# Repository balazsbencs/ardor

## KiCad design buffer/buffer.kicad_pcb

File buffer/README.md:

# Ardor Guitar Input Buffer

This folder contains the minimal guitar input buffer for Ardor.

Use this board between a passive guitar and the Raspberry Pi Codec Zero. Do
not connect a passive guitar directly to the Codec Zero input.

## KiCad project

Open [`buffer.kicad_pro`](buffer.kicad_pro) in KiCad to view or edit the
schematic and PCB.

Connect the guitar jack to `GUITAR_IN`. Connect `GUITAR_OUT` to the Codec Zero
input. Follow [`buffer.kicad_sch`](buffer.kicad_sch) for power and ground.

## JLCPCB assembly

The [`jlcpcb/production_files/`](jlcpcb/production_files/) folder contains
order-ready files for SMD assembly:

- [`GERBER-buffer.zip`](jlcpcb/production_files/GERBER-buffer.zip) contains the PCB files.
- [`BOM-buffer.csv`](jlcpcb/production_files/BOM-buffer.csv) contains the parts list.
- [`CPL-buffer.csv`](jlcpcb/production_files/CPL-buffer.csv) contains the part placement list.

Upload the Gerber, BOM, and CPL files to a JLCPCB PCB assembly order. Review
the parts and placement before you order.

The production files cover the SMD parts only. They do not include audio
jacks, wires, connectors, or enclosure parts. Add these parts after the board
arrives.

The larger [`hardware/control-io`](../hardware/control-io/README.md) and
[`hardware/integrated-codec-revc`](../hardware/integrated-codec-revc/README.md)
designs include their own guitar input stages. Choose one input design. Do not
place the standalone buffer in series with either design.

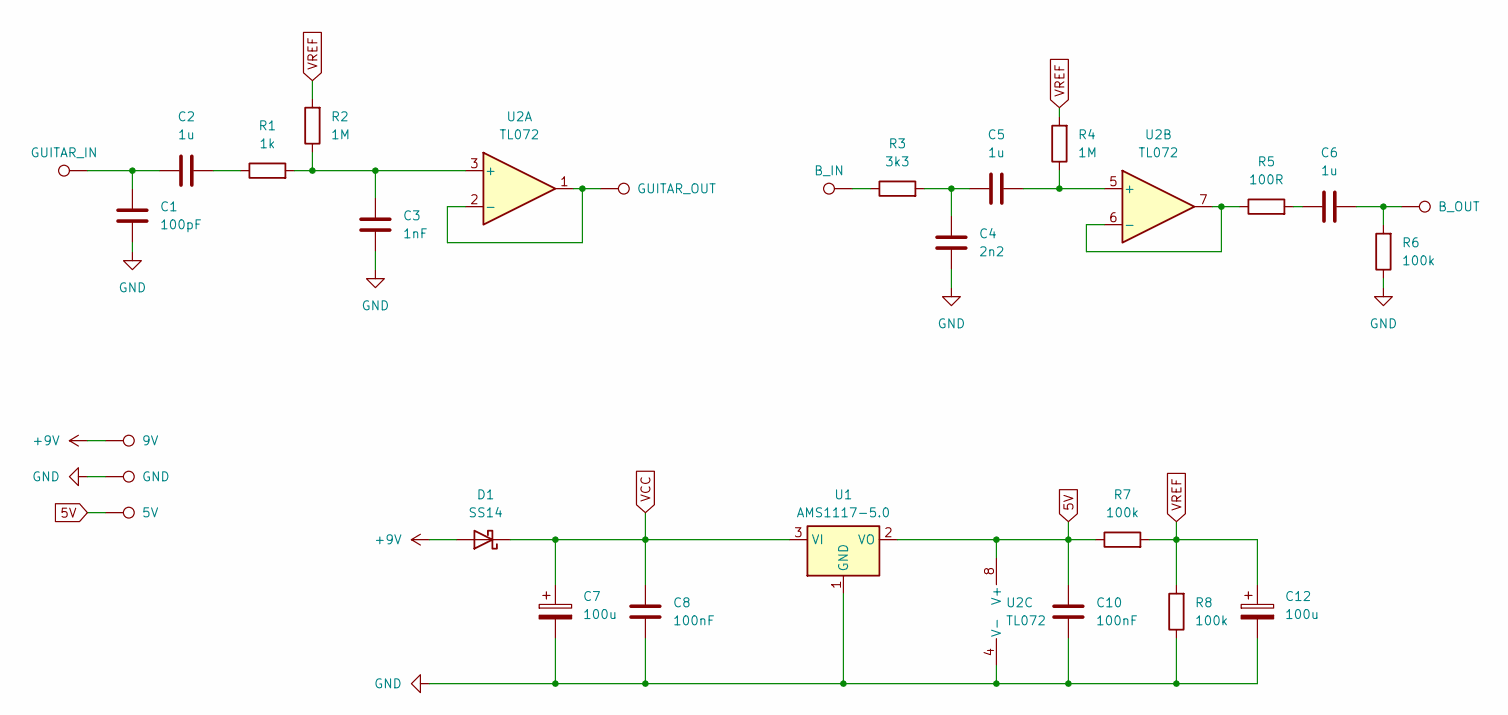
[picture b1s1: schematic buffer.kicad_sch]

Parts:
5V1: 5V; Pin_D1.0mm_L10.0mm_LooseFit
9V1: 9V; Pin_D1.0mm_L10.0mm_LooseFit
BUFFER_IN1: B_IN; Pin_D1.0mm_L10.0mm_LooseFit
C1: 100pF; C_0603_1608Metric
C2, C5, C6: 1u; C_0603_1608Metric
C3: 1nF; C_0603_1608Metric
C4: 2n2; C_0603_1608Metric
C7, C12: 100u; CP_Radial_D6.3mm_P2.50mm
C8, C10: 100nF; C_0603_1608Metric
D1: SS14; D_SMA
GIN1: GUITAR_IN; Pin_D1.0mm_L10.0mm_LooseFit
GND1: GND; Pin_D1.0mm_L10.0mm_LooseFit
GOUT1: GUITAR_OUT; Pin_D1.0mm_L10.0mm_LooseFit
OUT1: B_OUT; Pin_D1.0mm_L10.0mm_LooseFit
R1: 1k; R_0603_1608Metric
R2, R4: 1M; R_0603_1608Metric
R3: 3k3; R_0603_1608Metric
R5: 100R; R_0603_1608Metric
R6, R7, R8: 100k; R_0603_1608Metric
U1: AMS1117-5.0; SOT-223-3_TabPin2
U2: TL072; SOIC-8_3.9x4.9mm_P1.27mm

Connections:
5V: 5V1.1, C10.1, R7.1, U1.2 (VO), U2.8 (V+)
+9V: 9V1.1, D1.2 (A)
GND: C1.2, C3.2, C4.2, C7.2, C8.2, C10.2, C12.2, GND1.1, R6.1, R8.1, U1.1 (GND), U2.4 (V-)
unnamed: BUFFER_IN1.1, R3.1
unnamed: C1.1, C2.1, GIN1.1
unnamed: C2.2, R1.1
unnamed: C4.1, C5.1, R3.2
unnamed: C6.1, R5.2
unnamed: C6.2, OUT1.1, R6.2
unnamed: C3.1, R1.2, R2.1, U2.3 (+)
unnamed: GOUT1.1, U2.1, U2.2 (-)
unnamed: C5.2, R4.1, U2.5 (+)
unnamed: R5.1, U2.6 (-), U2.7
VCC: C7.1, C8.1, D1.1 (K), U1.3 (VI)
VREF: C12.1, R2.2, R4.2, R7.2, R8.2

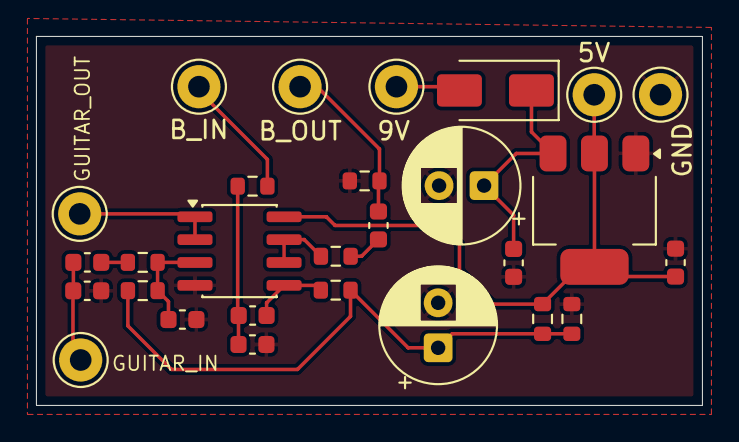
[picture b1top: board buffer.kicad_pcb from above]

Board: 2 copper layers, 37.0 x 20.5 mm, 28 parts (0 on the bottom side), 15 nets.

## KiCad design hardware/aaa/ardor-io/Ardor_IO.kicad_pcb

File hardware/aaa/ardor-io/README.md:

# Ardor Codec Zero I/O

Open **Ardor_IO.kicad_pro** in KiCad 9. The root schematic opens five functional sheets. **Ardor_IO.kicad_pcb** is the routed 68 × 46 mm compact board (45.7% less area than the previous 90 × 64 mm board; 60.9% less than the original 100 × 80 mm placement).

- **Ardor_IO.pdf** — printable six-sheet schematic.
- **BOM.csv** — component values, exact SMT manufacturer/JLCPCB part numbers and footprints.
- **[assembly/](assembly/README.md)** — stocked JLCPCB selections, BOM/CPL and Gerbers for **two boards, top-side SMT only**, plus the separate hand-assembly list.
- **DESIGN_NOTES.md** — wiring, GPIOs, signal levels, firmware sequence, layout guidance and production-release tests.
- **SOURCES.md** — primary data sheets and interface references.
- **verification/** — schematic ERC, exported netlist and connectivity audit.
- **routing/** — current board previews, placement coordinates, zero-violation DRC/parity report, pad/net audit and routing source/session. See [routing/README.md](routing/README.md).
- **footprints/** — project-local snapshots of the original package footprints, preserving their geometry across KiCad 9 library versions.
- **pcb-plan/** — historical, unrouted 100 × 80 mm placement; superseded by the current board.

Uses 5 V from the Pi, a 100 kΩ passive expression pedal, mono 6.3 mm line out, stereo headphones, DIN MIDI in and an internal feed to the separate amp circuit.

Rev A is a checked engineering prototype schematic, not a bench-qualified production release. Read the integration and release notes before building. Panel connector models and stack height are mechanical selections to be finalized with your PCB/enclosure.

The compact layout retains all 95 schematic components and the existing panel-harness interfaces. Connector functions/pins and testpoint signals are on front silkscreen; JP301 shunt instructions are on the back. Component references remain on F.Fab. Four M3 holes are provisional enclosure mounts, not a verified Raspberry Pi mounting pattern. Confirm mechanical fit and stack height before ordering.

C401/C402/C502/C601/C602 are now 10 µF / 50 V Samsung X7R ceramic capacitors (CL31B106KBHNNNE, JLCPCB C89632) in standard 1206 footprints. See [SMD capacitor selection](routing/SMD_CAPACITORS.md).

Review fixes (29 September 2026): Q501 is AO3400A; C501 is Panasonic EEEFK1C470P with manufacturer-specific local lands. The aluminium enclosure is bonded through audio jack sleeves; the MIDI input shell is insulated and unconnected. See [fix verification](review/FIXES.md) and the updated [connected single-page schematic](review/Ardor_IO_connected.pdf).

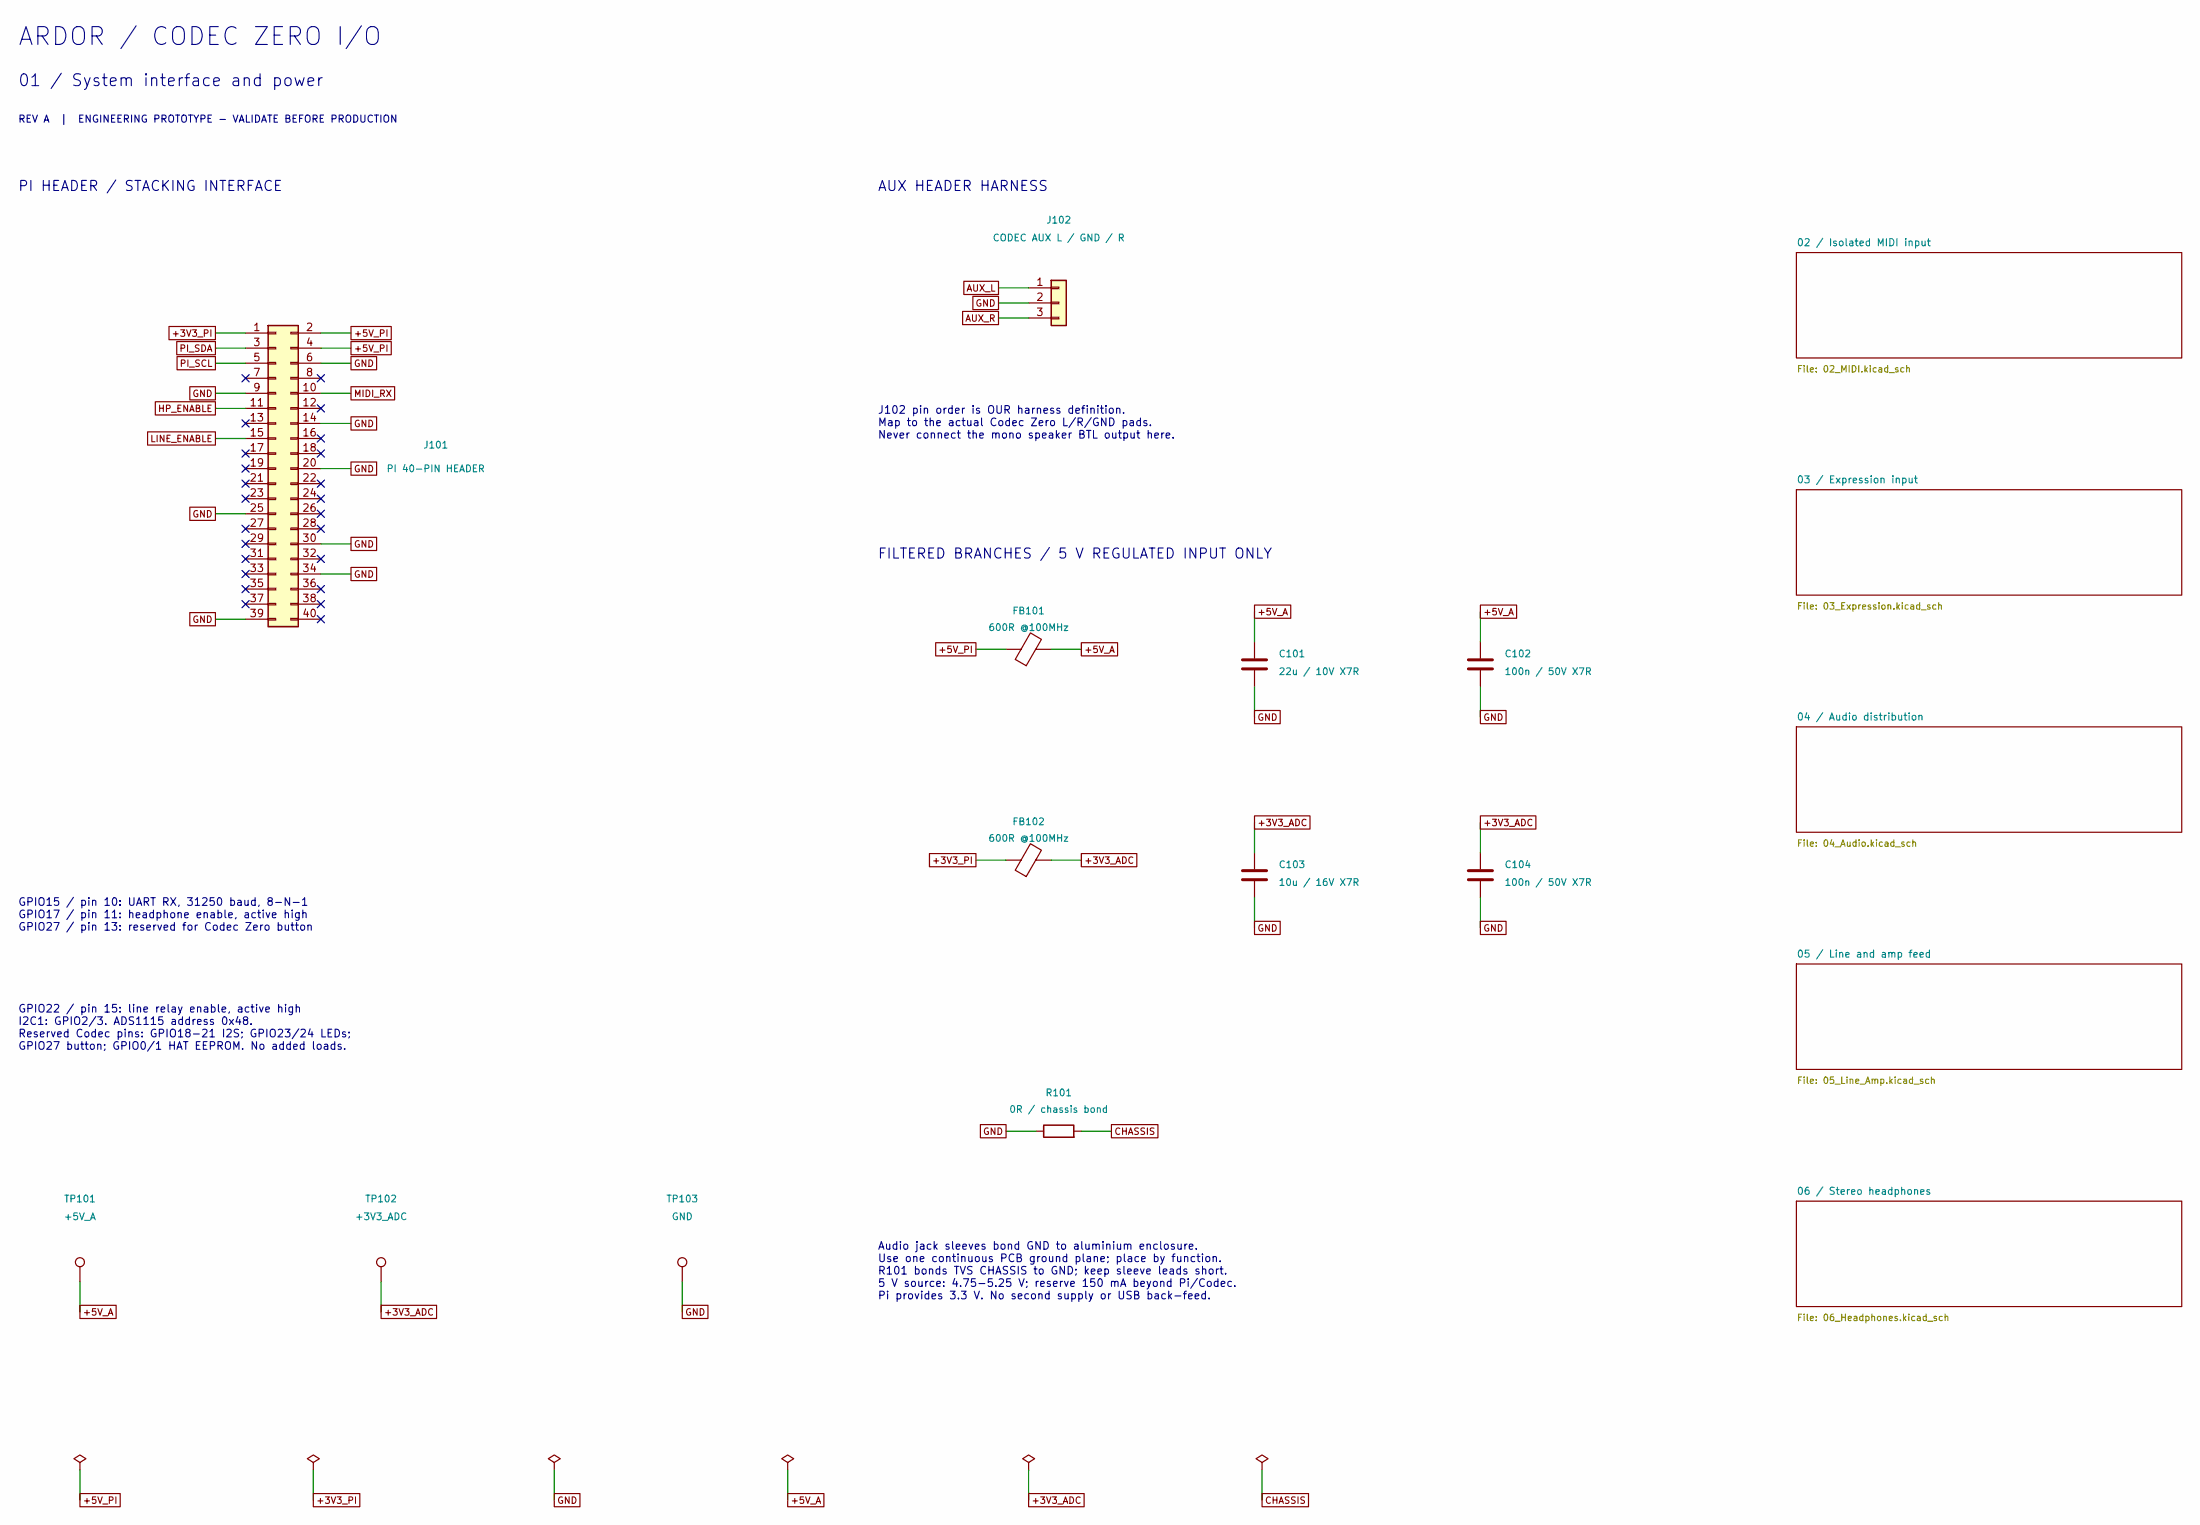
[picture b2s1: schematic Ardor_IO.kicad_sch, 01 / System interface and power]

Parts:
C101: 22u / 10V X7R; C_0805_2012Metric; MPN Murata GRM21BZ71A226ME15L; JLCPCB Part # C907991
C102, C104: 100n / 50V X7R; C_0603_1608Metric; MPN YAGEO CC0603KRX7R9BB104; JLCPCB Part # C14663
C103: 10u / 16V X7R; C_0805_2012Metric; MPN Samsung CL21B106KOQNNNE; JLCPCB Part # C95841
FB101: 600R @100MHz; L_0805_2012Metric; MPN Murata BLM21PG601SN1D; JLCPCB Part # C41556732
FB102: 600R @100MHz; R_0603_1608Metric; MPN Murata BLM18AG601SN1D; JLCPCB Part # C19330
J101: PI 40-PIN HEADER; PinSocket_2x20_P2.54mm_Vertical; MPN Samtec SSQ-120-03-G-D (verify stack hei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
J102: CODEC AUX L / GND / R; PinHeader_1x03_P2.54mm_Vertical
R101: 0R / chassis bond; R_1206_3216Metric; MPN UNI-ROYAL 1206W4F0000T5E; JLCPCB Part # C17888
TP101: +5V_A; TestPoint_Pad_D1.5mm
TP102: +3V3_ADC; TestPoint_Pad_D1.5mm
TP103: GND; TestPoint_Pad_D1.5mm

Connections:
+3V3_ADC: C103.1, C104.1, FB102.2, TP102.1; also elsewhere on the board
+3V3_PI: FB102.1, J101.1; also elsewhere on the board
+5V_A: C101.1, C102.1, FB101.2, TP101.1; also elsewhere on the board
+5V_PI: FB101.1, J101.2, J101.4; also elsewhere on the board
AUX_L: J102.1; also elsewhere on the board
AUX_R: J102.3; also elsewhere on the board
CHASSIS: R101.2; also elsewhere on the board
GND: C101.2, C102.2, C103.2, C104.2, J101.6, J101.9, J101.14, J101.20, J101.25, J101.30, J101.34, J101.39, J102.2, R101.1, TP103.1; also elsewhere on the board
HP_ENABLE: J101.11; also elsewhere on the board
LINE_ENABLE: J101.15; also elsewhere on the board
MIDI_RX: J101.10; also elsewhere on the board
PI_SCL: J101.5; also elsewhere on the board
PI_SDA: J101.3; also elsewhere on the board

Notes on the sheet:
ARDOR / CODEC ZERO I/O
01 / System interface and power
REV A | ENGINEERING PROTOTYPE - VALIDATE BEFORE PRODUCTION
PI HEADER / STACKING INTERFACE
GPIO15 / pin 10: UART RX, 31250 baud, 8-N-1 GPIO17 / pin 11: headphone enable, active high GPIO27 / pin 13: reserved for Codec Zero button
GPIO22 / pin 15: line relay enable, active high I2C1: GPIO2/3. ADS1115 address 0x48. Reserved Codec pins: GPIO18-21 I2S; GPIO23/24 LEDs; GPIO27 button; GPIO0/1 HAT EEPROM. No added loads.
AUX HEADER HARNESS
J102 pin order is OUR harness definition. Map to the actual Codec Zero L/R/GND pads. Never connect the mono speaker BTL output here.
FILTERED BRANCHES / 5 V REGULATED INPUT ONLY
Audio jack sleeves bond GND to aluminium enclosure. Use one continuous PCB ground plane; place by function. R101 bonds TVS CHASSIS to GND; keep sleeve leads short. 5 V source: 4.75-5.25 V; reserve 150 mA beyond Pi/Codec. Pi provides 3.3 V. No second supply or USB back-feed.

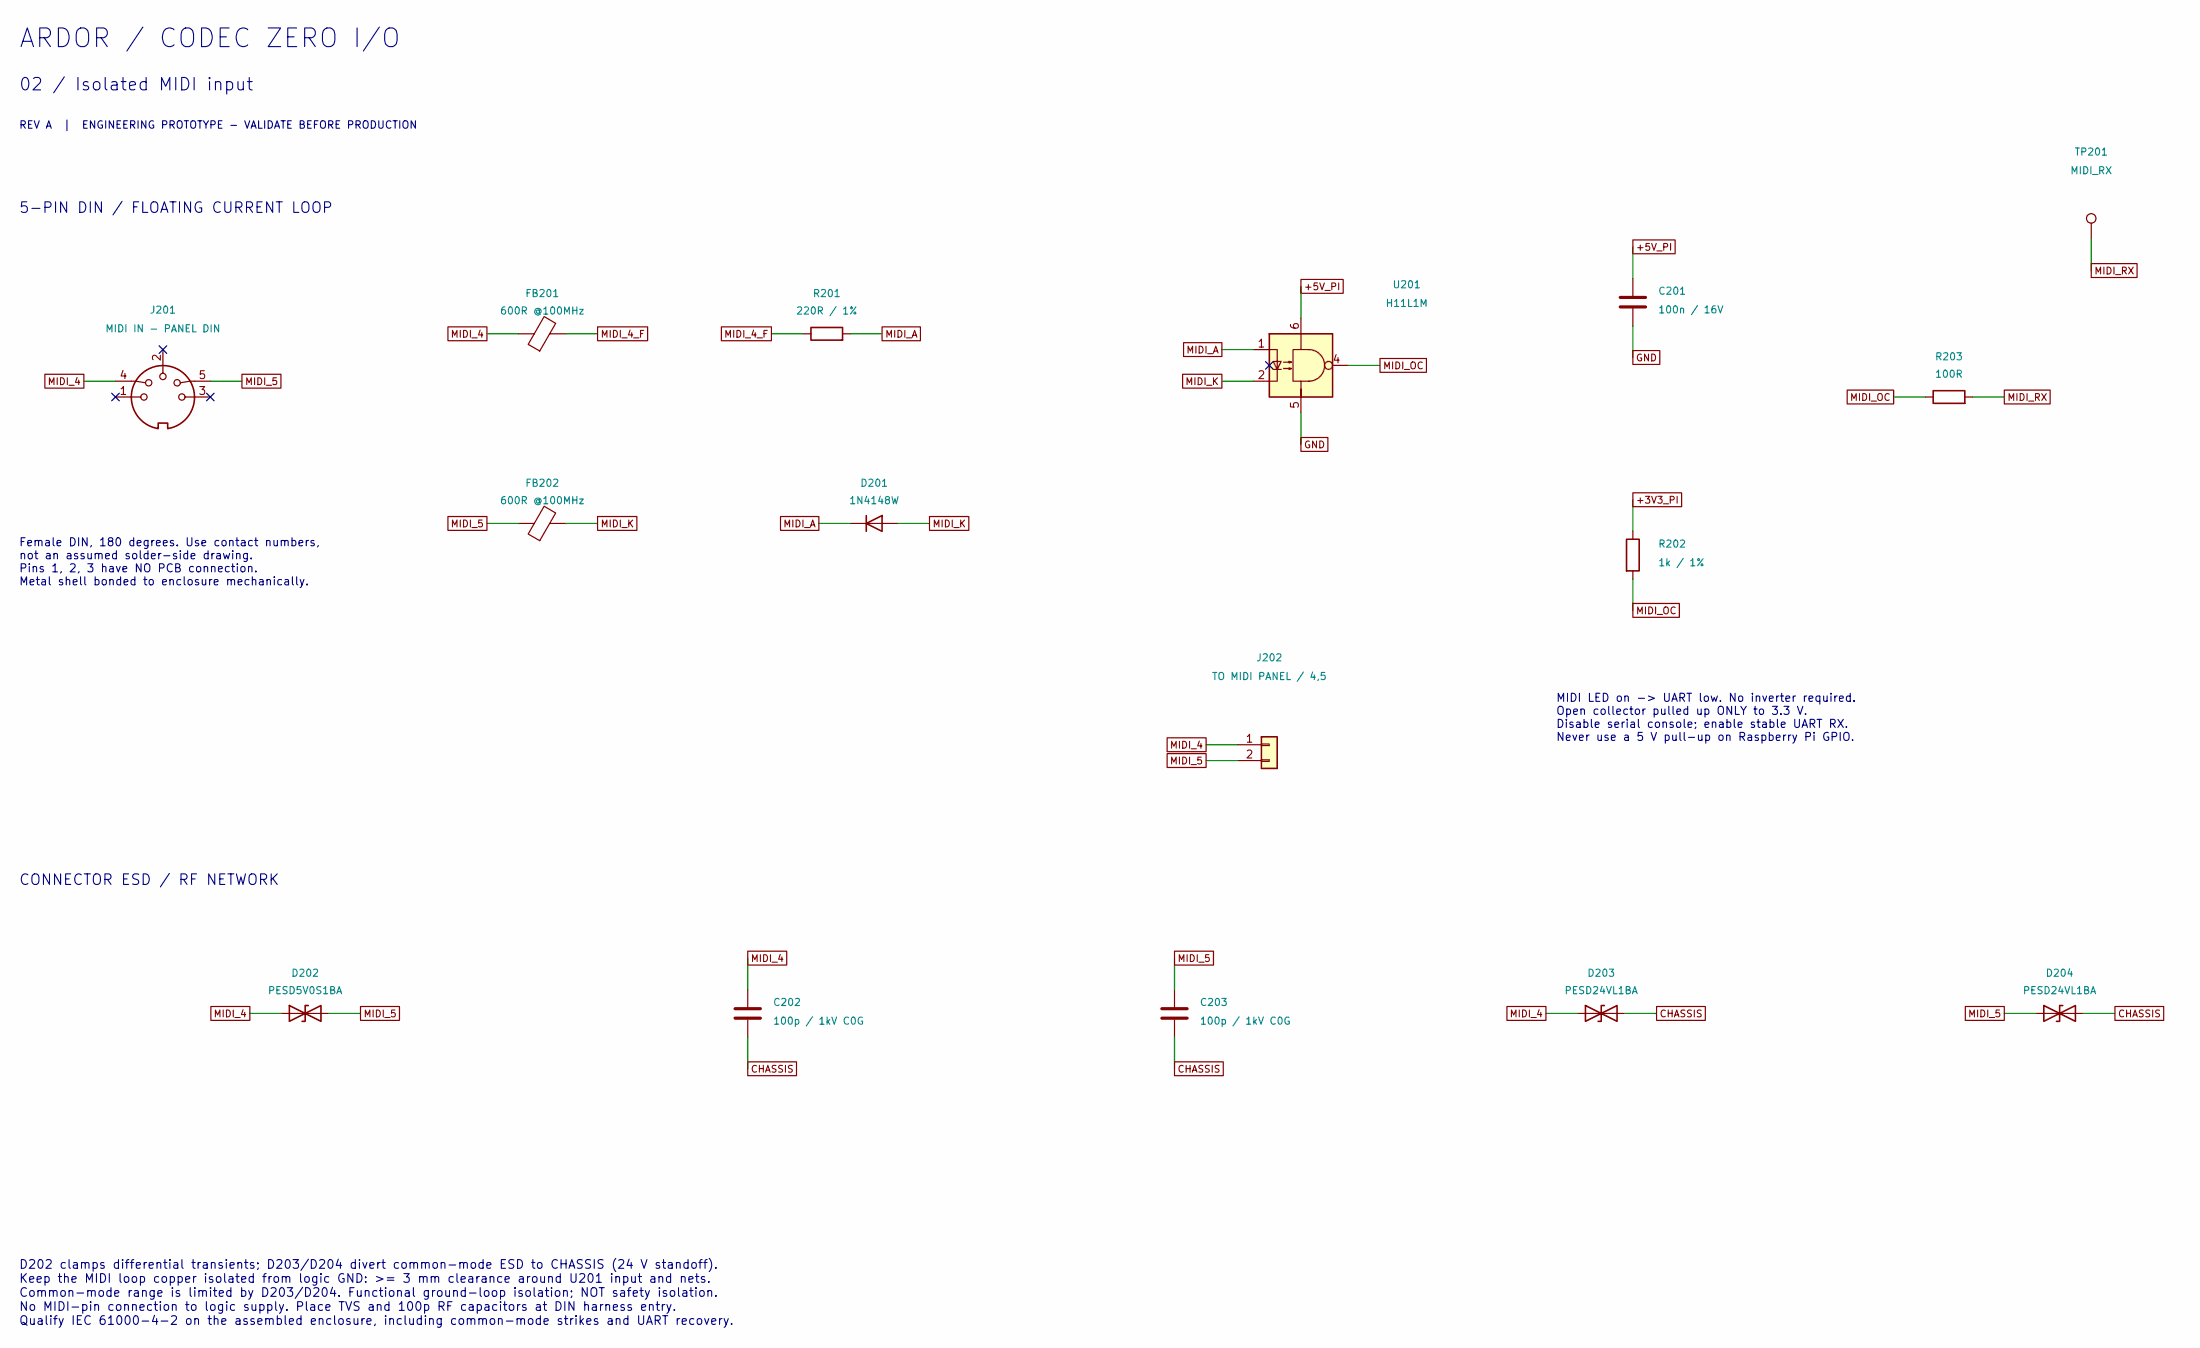
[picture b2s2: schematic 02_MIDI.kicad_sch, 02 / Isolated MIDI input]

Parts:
C201: 100n / 16V; C_0603_1608Metric
C202, C203: 100p / 1kV C0G; C_1206_3216Metric
D201: 1N4148W; D_SOD-123; MPN 1N4148W
D202: PESD5V0S1BA; D_SOD-323; MPN Nexperia PESD5V0S1BA
D203, D204: PESD24VL1BA; D_SOD-323; MPN Nexperia PESD24VL1BA
FB201, FB202: 600R @100MHz; R_0603_1608Metric; MPN Murata BLM18AG601SN1D
J201: MIDI IN - PANEL DIN
J202: TO MIDI PANEL / 4,5; PinHeader_1x02_P2.54mm_Vertical
R201: 220R / 1%; R_0603_1608Metric
R202: 1k / 1%; R_0603_1608Metric
R203: 100R; R_0603_1608Metric
TP201: MIDI_RX; TestPoint_Pad_D1.5mm
U201: H11L1M; DIP-6_W7.62mm; MPN onsemi H11L1M

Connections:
+3V3_PI: R202.1; also elsewhere on the board
+5V_PI: C201.1, U201.6; also elsewhere on the board
CHASSIS: C202.2, C203.2, D203.2 (A2), D204.2 (A2); also elsewhere on the board
GND: C201.2, U201.5; also elsewhere on the board
MIDI_4: C202.1, D202.1 (A1), D203.1 (A1), FB201.1, J201.4, J202.1
MIDI_4_F: FB201.2, R201.1
MIDI_5: C203.1, D202.2 (A2), D204.1 (A1), FB202.1, J201.5, J202.2
MIDI_A: D201.1 (K), R201.2, U201.1
MIDI_K: D201.2 (A), FB202.2, U201.2
MIDI_OC: R202.2, R203.1, U201.4
MIDI_RX: R203.2, TP201.1; also elsewhere on the board

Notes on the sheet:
ARDOR / CODEC ZERO I/O
02 / Isolated MIDI input
REV A | ENGINEERING PROTOTYPE - VALIDATE BEFORE PRODUCTION
5-PIN DIN / FLOATING CURRENT LOOP
Female DIN, 180 degrees. Use contact numbers, not an assumed solder-side drawing. Pins 1, 2, 3 have NO PCB connection. Metal shell bonded to enclosure mechanically.
MIDI LED on -> UART low. No inverter required. Open collector pulled up ONLY to 3.3 V. Disable serial console; enable stable UART RX. Never use a 5 V pull-up on Raspberry Pi GPIO.
CONNECTOR ESD / RF NETWORK
D202 clamps differential transients; D203/D204 divert common-mode ESD to CHASSIS (24 V standoff). Keep the MIDI loop copper isolated from logic GND: >= 3 mm clearance around U201 input and nets. Common-mode range is limited by D203/D204. Functional ground-loop isolation; NOT safety isolation. No MI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

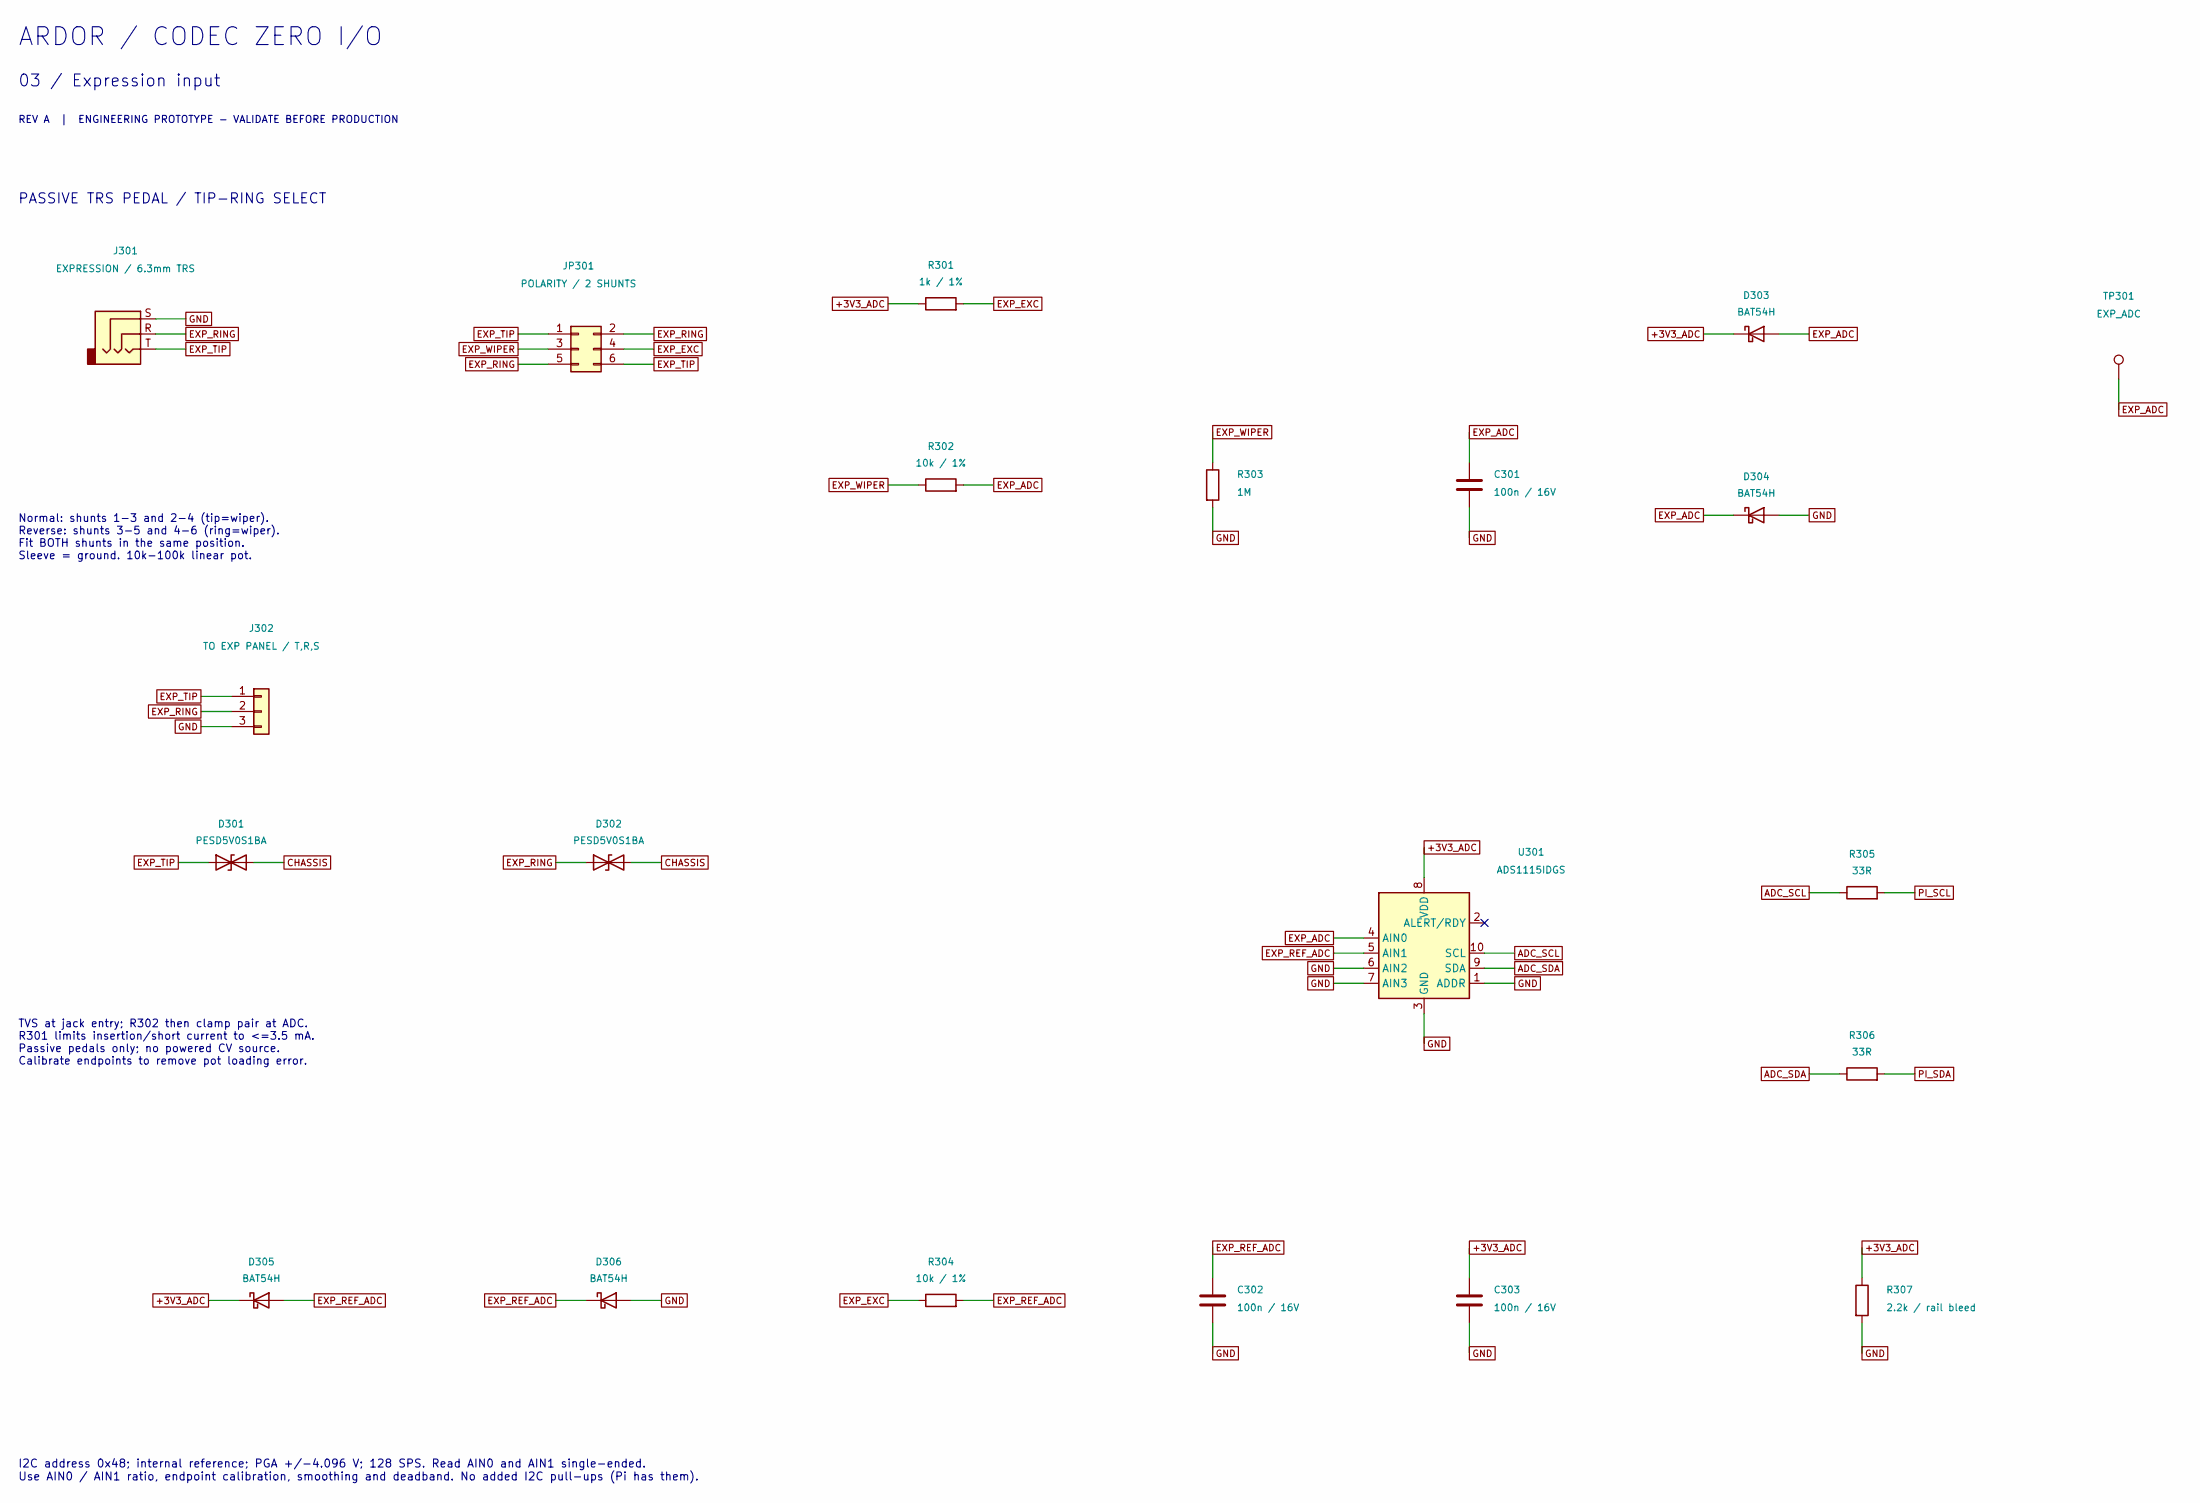
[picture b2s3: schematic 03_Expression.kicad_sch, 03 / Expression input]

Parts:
C301, C302, C303: 100n / 16V; C_0603_1608Metric
D301, D302: PESD5V0S1BA; D_SOD-323; MPN Nexperia PESD5V0S1BA
D303, D304, D305, D306: BAT54H; D_SOD-123F; MPN Nexperia BAT54H,115
J301: EXPRESSION / 6.3mm TRS
J302: TO EXP PANEL / T,R,S; PinHeader_1x03_P2.54mm_Vertical
JP301: POLARITY / 2 SHUNTS; PinHeader_2x03_P2.54mm_Vertical
R301: 1k / 1%; R_0603_1608Metric
R302, R304: 10k / 1%; R_0603_1608Metric
R303: 1M; R_0603_1608Metric
R305, R306: 33R; R_0603_1608Metric
R307: 2.2k / rail bleed; R_0603_1608Metric
TP301: EXP_ADC; TestPoint_Pad_D1.5mm
U301: ADS1115IDGS; VSSOP-10_3x3mm_P0.5mm; MPN TI ADS1115IDGSR

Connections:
+3V3_ADC: C303.1, D303.1 (K), D305.1 (K), R301.1, R307.1, U301.8 (VDD); also elsewhere on the board
ADC_SCL: R305.1, U301.10 (SCL)
ADC_SDA: R306.1, U301.9 (SDA)
CHASSIS: D301.2 (A2), D302.2 (A2); also elsewhere on the board
EXP_ADC: C301.1, D303.2 (A), D304.1 (K), R302.2, TP301.1, U301.4 (AIN0)
EXP_EXC: JP301.4, R301.2, R304.1
EXP_REF_ADC: C302.1, D305.2 (A), D306.1 (K), R304.2, U301.5 (AIN1)
EXP_RING: D302.1 (A1), J301.R, J302.2, JP301.2, JP301.5
EXP_TIP: D301.1 (A1), J301.T, J302.1, JP301.1, JP301.6
EXP_WIPER: JP301.3, R302.1, R303.1
GND: C301.2, C302.2, C303.2, D304.2 (A), D306.2 (A), J301.S, J302.3, R303.2, R307.2, U301.1 (ADDR), U301.3 (GND), U301.6 (AIN2), U301.7 (AIN3); also elsewhere on the board
PI_SCL: R305.2; also elsewhere on the board
PI_SDA: R306.2; also elsewhere on the board

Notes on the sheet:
ARDOR / CODEC ZERO I/O
03 / Expression input
REV A | ENGINEERING PROTOTYPE - VALIDATE BEFORE PRODUCTION
PASSIVE TRS PEDAL / TIP-RING SELECT
Normal: shunts 1-3 and 2-4 (tip=wiper). Reverse: shunts 3-5 and 4-6 (ring=wiper). Fit BOTH shunts in the same position. Sleeve = ground. 10k-100k linear pot.
TVS at jack entry; R302 then clamp pair at ADC. R301 limits insertion/short current to <=3.5 mA. Passive pedals only; no powered CV source. Calibrate endpoints to remove pot loading error.
I2C address 0x48; internal reference; PGA +/-4.096 V; 128 SPS. Read AIN0 and AIN1 single-ended. Use AIN0 / AIN1 ratio, endpoint calibration, smoothing and deadband. No added I2C pull-ups (Pi has them).

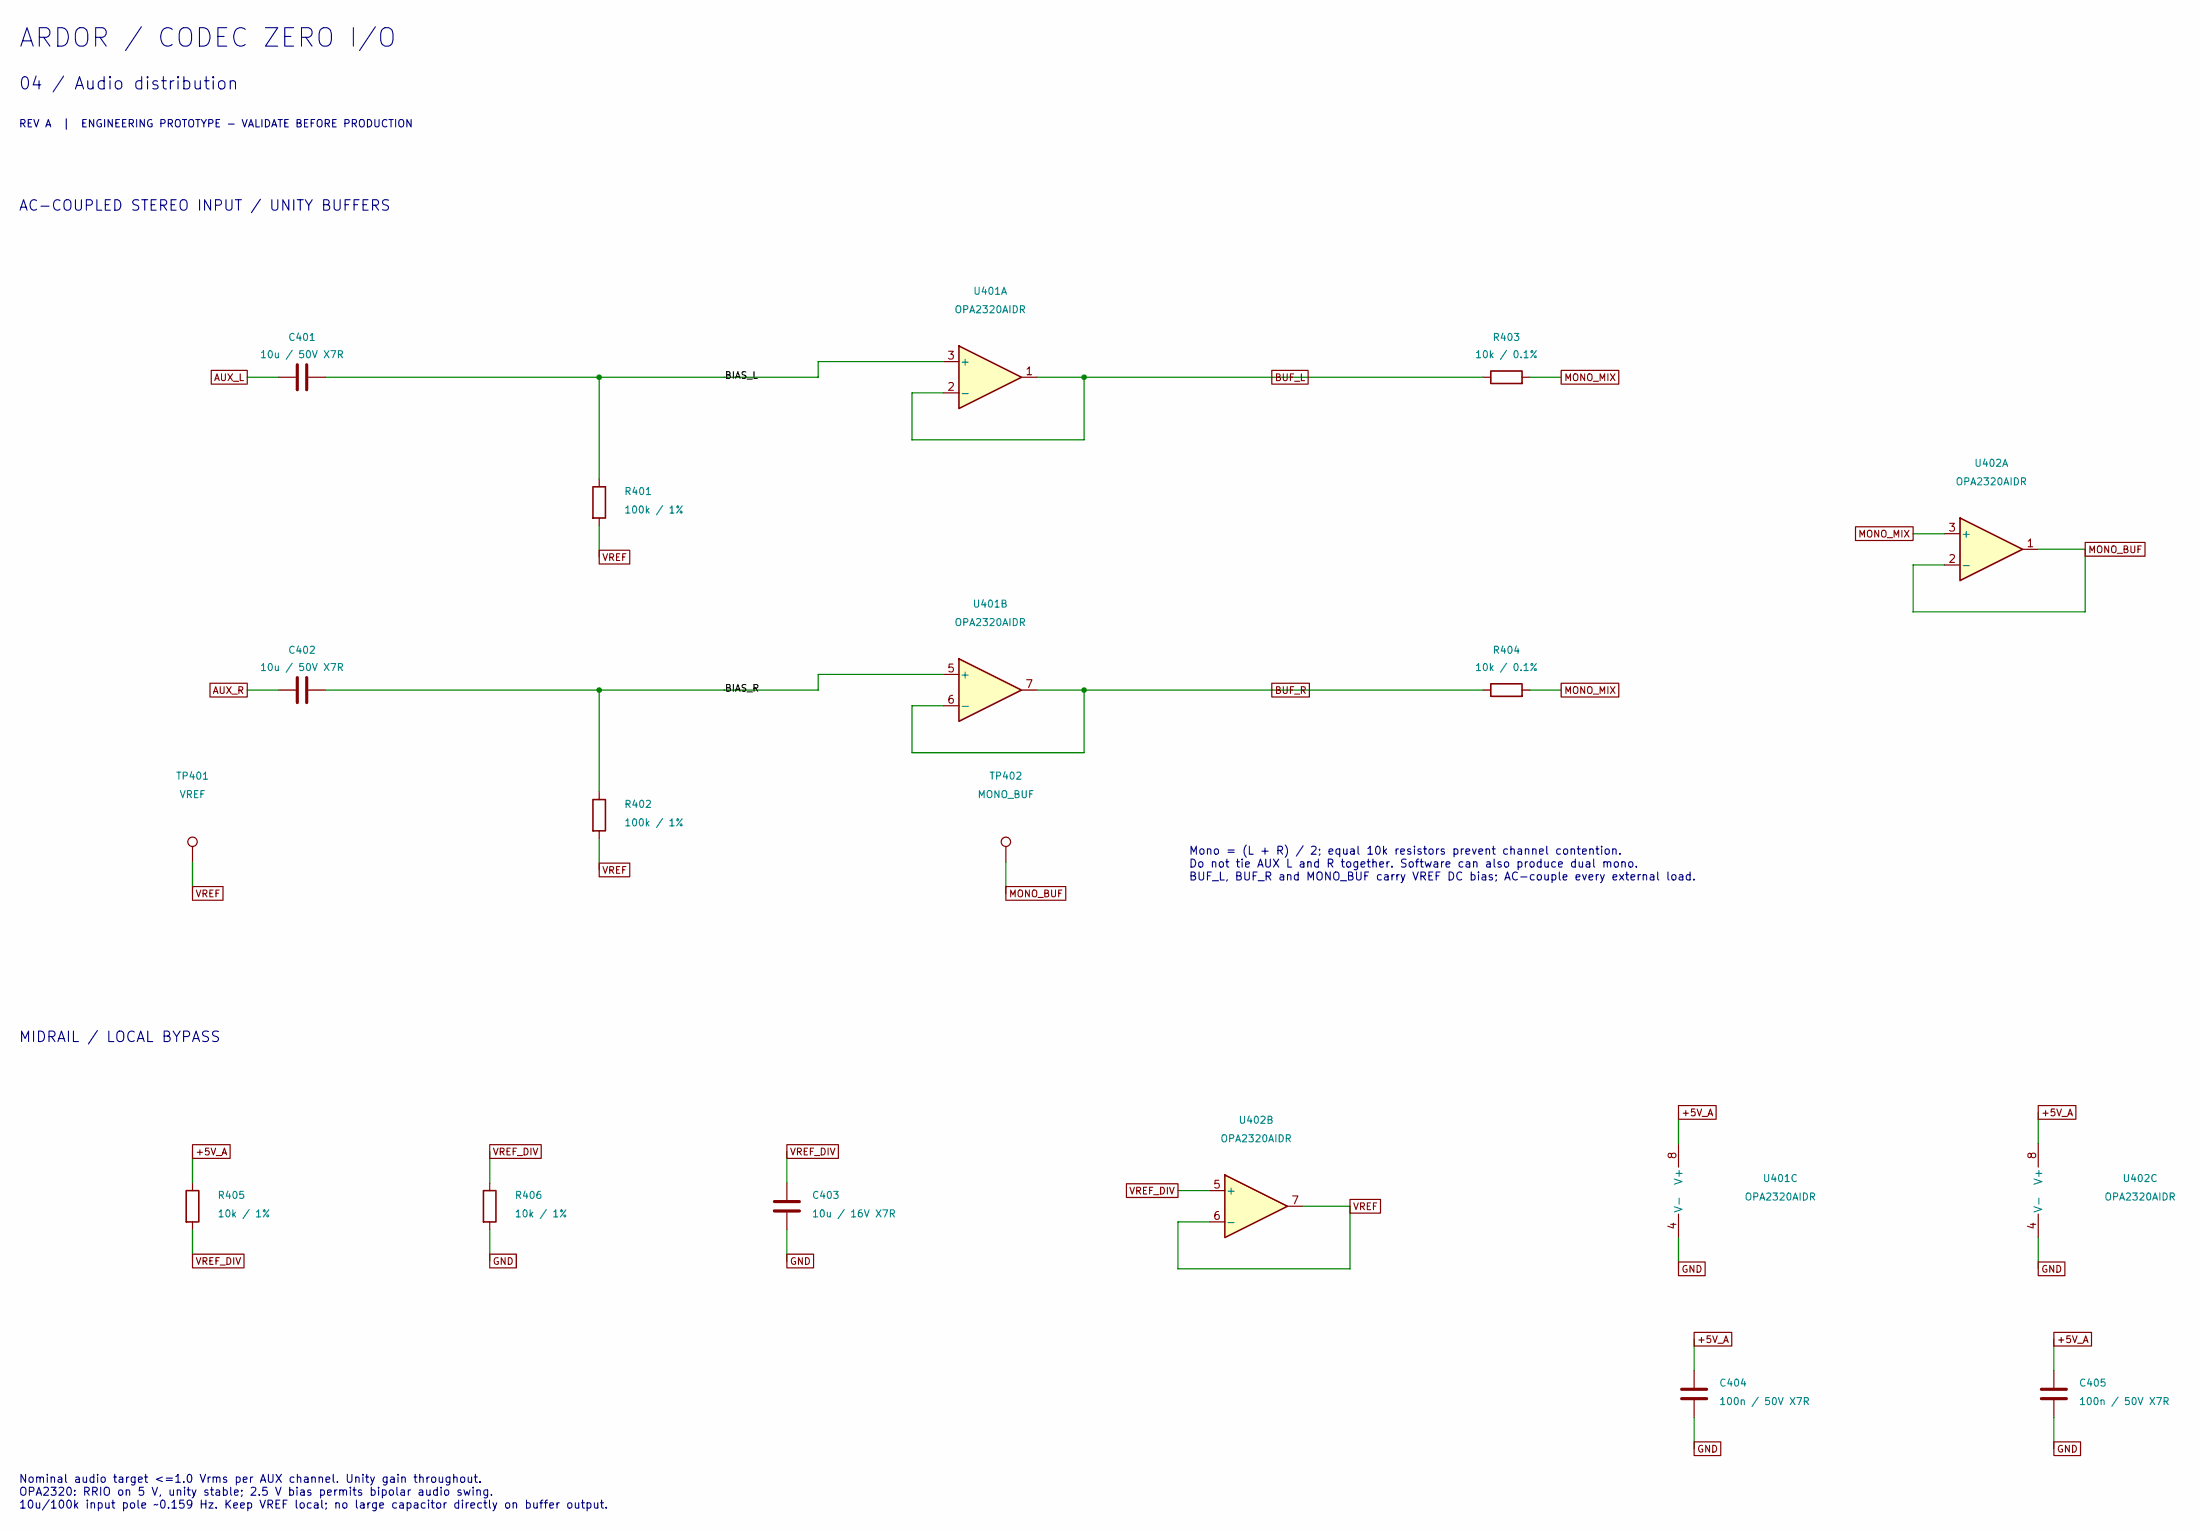
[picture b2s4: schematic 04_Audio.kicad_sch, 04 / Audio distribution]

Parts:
C401, C402: 10u / 50V X7R; C_1206_3216Metric; MPN Samsung CL31B106KBHNNNE; JLCPCB Part # C89632
C403: 10u / 16V X7R; C_0805_2012Metric; MPN Samsung CL21B106KOQNNNE; JLCPCB Part # C95841
C404, C405: 100n / 50V X7R; C_0603_1608Metric; MPN YAGEO CC0603KRX7R9BB104; JLCPCB Part # C14663
R401, R402: 100k / 1%; R_0603_1608Metric; MPN UNI-ROYAL 0603WAF1003T5E; JLCPCB Part # C25803
R403, R404: 10k / 0.1%; R_0603_1608Metric; MPN YAGEO RT0603BRD0710KL; JLCPCB Part # C95204
R405, R406: 10k / 1%; R_0603_1608Metric; MPN UNI-ROYAL 0603WAF1002T5E; JLCPCB Part # C25804
TP401: VREF; TestPoint_Pad_D1.5mm
TP402: MONO_BUF; TestPoint_Pad_D1.5mm
U401, U402: OPA2320AIDR; SOIC-8_3.9x4.9mm_P1.27mm; MPN TI OPA2320AIDR; JLCPCB Part # C2863402

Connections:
+5V_A: C404.1, C405.1, R405.1, U401.8 (V+), U402.8 (V+); also elsewhere on the board
/04 / Audio distribution/BIAS_L: C401.2, R401.1, U401.3 (+)
/04 / Audio distribution/BIAS_R: C402.2, R402.1, U401.5 (+)
AUX_L: C401.1; also elsewhere on the board
AUX_R: C402.1; also elsewhere on the board
BUF_L: R403.1, U401.1, U401.2 (-); also elsewhere on the board
BUF_R: R404.1, U401.6 (-), U401.7; also elsewhere on the board
GND: C403.2, C404.2, C405.2, R406.2, U401.4 (V-), U402.4 (V-); also elsewhere on the board
MONO_BUF: TP402.1, U402.1, U402.2 (-); also elsewhere on the board
MONO_MIX: R403.2, R404.2, U402.3 (+)
VREF: R401.2, R402.2, TP401.1, U402.6 (-), U402.7
VREF_DIV: C403.1, R405.2, R406.1, U402.5 (+)

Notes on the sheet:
ARDOR / CODEC ZERO I/O
04 / Audio distribution
REV A | ENGINEERING PROTOTYPE - VALIDATE BEFORE PRODUCTION
AC-COUPLED STEREO INPUT / UNITY BUFFERS
Mono = (L + R) / 2; equal 10k resistors prevent channel contention. Do not tie AUX L and R together. Software can also produce dual mono. BUF_L, BUF_R and MONO_BUF carry VREF DC bias; AC-couple every external load.
MIDRAIL / LOCAL BYPASS
Nominal audio target <=1.0 Vrms per AUX channel. Unity gain throughout. OPA2320: RRIO on 5 V, unity stable; 2.5 V bias permits bipolar audio swing. 10u/100k input pole ~0.159 Hz. Keep VREF local; no large capacitor directly on buffer output.
